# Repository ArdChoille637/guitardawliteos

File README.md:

# GuitarDAWLiteOS

Bare-metal **Raspberry Pi 5** loop recorder / guitarist workbench. I²S audio (PCM1808 ADC + PCM5102A DAC), SD recording, a plain display (no touch) with **5 rotary-encoder knobs + a sustain-pedal footswitch** as the interface — **no OS, no USB in the audio path.** Built on the [Circle](https://github.com/rsta2/circle) bare-metal framework (GPLv3).

> **This is the project front door.** Everything links from here.

## Status — 2026-07-10
- 🎉 **FIRST HARDWARE BOOT — success, first try.** Pi 5 (2GB) booted the M3 audio-engine kernel over HDMI: all 4 cores up, `I2S full duplex (TXRX): RUNNING`, capture counting **exactly 48,000 frames/s**, zero drops, zero ring overruns, storage drain at exactly the audio rate, thermal loop live. Milestone 0 ✅, Spike A ✅ (RP1 proven by the running I²S DMA itself), M3 engine verified live (codecs still to wire).
- ✅ **Research verified.** 29 load-bearing claims checked against primary sources. 6 were wrong; 3 of those change the build. → [docs/claim-verification.md](docs/claim-verification.md)
- ✅ **Spike B done.** Internal MCLK route impossible (`clk_i2s` is claimed by BCLK); an Arduino Nano ESP32 generates 12.2880 MHz instead, bench-verified via its own PCNT peripheral. → [esp32-mclk/](esp32-mclk/)
- ✅ **Milestone 3 code live** — full-duplex I²S monitor path (~1.0 ms worst-case in→out), lock-free SPMC broadcast ring (seqlock reserve/commit; host tests caught a real torn-read bug pre-hardware; passes plain + ThreadSanitizer), 4-core split. Adversarially reviewed (5 lenses, 2 rounds); the review caught a critical `KERNEL_MAX_SIZE` boot-blocker before first boot. → [src/](src/), [tests/](tests/), [planning/build-plan.md](planning/build-plan.md)
- ⏭️ **Next: Milestone 2 wiring** — breadboard the codecs + front-end per [docs/breadboard-build.md](docs/breadboard-build.md) (DAC playback first for the fastest win), Nano ESP32 → PCM1808 SCKI, then the M3 gate: clean tone in→out, 10 min, zero underruns.

## The 6 things verification changed (read before building)
1. **No `≤128` DMA chunk cap** — it's a constructor arg, default **8192**. Ring-buffer/SD batching gets *easier*. The doc was wrong.
2. **Pi 5 SD = BCM2712 SDHCI (`CEMMCDevice`, `0x1000FFF000`), not RP1, not `CSDHCIDevice`.** Tested & supported.
3. **Do NOT add `pciex4_reset=0`** with Circle — Circle brings up the PCIe root complex itself. Stock `config.txt`.
4. **MCLK cannot come from the Pi 5's own GPIO while I²S is running.** `clk_i2s` — the only RP1 clock generator with `pll_audio` as a parent — is already claimed for BCLK. **→ external MCLK generator (Nano ESP32), see Spike B above.**
5. **The two "MIT" libs (simplecodec3, Yin-Pitch-Tracking) are unlicensed** (all-rights-reserved). YIN patent is **expired** → clean-room reimplement from the 2002 paper.
6. **(2026-07-09)** Even the *revised* internal-MCLK mechanism from correction #4 (`clk_i2s→clk_gp0→GPIO4`) turned out to be a resource conflict, not just missing Circle code — see [claim-verification.md](docs/claim-verification.md).

## Hardware (Phase 1)
- Raspberry Pi 5 · microSD (Class-10/UHS-I) · HDMI monitor ≤1080p · USB-serial for the UART debug console.
- PCM1808 ADC (**bus master**, strap-only) · PCM5102A / GY-PCM5102 DAC (strap-only).
- **Arduino Nano ESP32** — external MCLK generator (see [esp32-mclk/](esp32-mclk/)), electrically independent of the Pi 5 except for the MCLK line + shared ground.

**Verified pin map** ([details](planning/build-plan.md#milestone-2--hardware-bring-up-i²s-loopback)) — **the PCM1808 masters the I²S bus** (2026-07-10 pivot: two free-running crystals can't stay fs-locked, so the ADC divides the Nano's MCLK into BCK/LRCK and the Pi runs I²S slave — see [docs/claim-verification.md](docs/claim-verification.md)):

| Source | Signal | → |
|--:|---|---|
| **PCM1808 BCK** | BCLK 3.072 MHz (ADC-driven) | Pi GPIO18 + DAC BCK |
| **PCM1808 LRCK** | LRCLK 48 kHz (ADC-driven) | Pi GPIO19 + DAC LCK |
| PCM1808 DOUT | data IN (capture) | → Pi GPIO20 |
| Pi GPIO21 | data OUT (playback) | → PCM5102A DIN |
| **Nano ESP32 D2/GPIO5** | MCLK 12.288 MHz | → PCM1808 SCKI only |

⚠️ **PCM5102A breakout: set the XSMT pad HIGH (unmute)** — ships muted. ⚠️ **PCM1808: strap MD1=MD0=HIGH (master 256fs), FMT=GND, before power-on** — board-specific pin table in [docs/adc-hookup.md](docs/adc-hookup.md).

## Map
- **[planning/build-plan.md](planning/build-plan.md)** — milestones 0–6, tasks with effort, risk register, pinned dependencies.
- **[docs/claim-verification.md](docs/claim-verification.md)** — full verdict table + 6 consequential corrections with sources.
- **[docs/hardware-review.md](docs/hardware-review.md)** — datasheet-verified BOM, power tree, connection/netlist table, **guitar front-end design**, grounding, risk register.
- **[docs/schematic.md](docs/schematic.md)** — buildable schematic: refdes BOM, net-by-net netlist, **SPICE-verified** front-end, build order, ERC self-check (netlist = rev-A Pi-as-master; see its pivot banner). Sheets: [front-end 5 V](docs/frontend-schematic.svg) · [front-end 9 V TL072 (as-built)](docs/tl072-frontend-schematic.svg) · [codec & clocks (as-built)](docs/codec-power-schematic.svg). Sim: [sim/](docs/sim/).
- **[docs/wiring-diagram.svg](docs/wiring-diagram.svg)** — as-built bench wiring overview (Nano MCLK → PCM1808 **bus master** → Pi 5 slave + PCM5102A; clocks/data/power domains).
- **[kicad/](kicad/)** — openable **KiCad project** (`guitardawliteos.kicad_pro`, KiCad-10-verified) + generated netlist/symbols/BOM from `gen.py` (ERC-checked). See [kicad/README.md](kicad/README.md).
- **[docs/pcb-learning-path.md](docs/pcb-learning-path.md)** — **follow-along PCB-design curriculum + open-hardware roadmap** (M1 board-from-netlist → M4 Pi 5 HAT → M6 rev-B HAT+ → M7 faceplate → M8 retro deck → M9 CM5 carrier), hackability + licensing.
- **[docs/parts-order.md](docs/parts-order.md)** — **DigiKey prototyping order** (verified live 2026-07-01): breadboard + codecs + front-end + tape Level A + Touch Display 2, with MPNs, quantities, substitutions for dead parts, and the not-DigiKey list.
- **[docs/retro-deck-design.md](docs/retro-deck-design.md)** — **Phase-2 architecture (verified; UI pivot 2026-07-23)**: **5 rotary encoders + sustain pedal + display-only panel** (TD2 via `rp1dsi` with `bEnableTouch=FALSE`, zero GPIO — or plain HDMI; SPI TFT ruled out), cassette tape loop as analog insert (Level A ships in rev B, VINR return + REM punch-in), three-layer retro mechanicals, recomputed rev-B GPIO budget (J8 fully allocated + MCP23017 expander).
- **[docs/breadboard-build.md](docs/breadboard-build.md)** + [breadboard-layout.svg](docs/breadboard-layout.svg) — solderless build with the GY modules + a DIP op-amp; placement + step-by-step + gotcha checklist.
- **[docs/adc-hookup.md](docs/adc-hookup.md)** — **bench card: every wire for Pi 5 + PCM1808 + Nano ESP32 capture hookup** (power, ground, straps, clocks, data, order of operations).
- **[docs/tl072-frontend.md](docs/tl072-frontend.md)** — **drawer-parts front-end variant: TL072 on 9 V** (SPICE-verified; two changes from the canonical schematic) + CD4053BE rev-B notes. Schematic sheet: [tl072-frontend-schematic.svg](docs/tl072-frontend-schematic.svg).
- **[docs/build-setup.md](docs/build-setup.md)** — toolchain, build, SD flash, UART.
- **[docs/debug-probe.md](docs/debug-probe.md)** — **Raspberry Pi Debug Probe on the Pi 5**: UART console (mode A) vs. SWD breakpoint debugging of all four cores (mode B), cabling, and the GPIO14/15 conflict with the encoder pinout.
- Original Phase-1 research reference: project `CLAUDE.md` (the GuitarDAWLiteOS research doc).

## Build foundation (pinned)
Circle `develop` @ `22722a7` · `RASPPI=5` → `kernel_2712.img` · FatFs R0.16 (`addon/fatfs`) · YIN clean-room.

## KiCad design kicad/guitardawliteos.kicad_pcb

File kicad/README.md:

# GuitarDAWLiteOS — KiCad project files

> ⚠️ **This netlist is rev-A (Pi-as-master) and predates the 2026-07-10 clock pivot.** `gen.py` still routes
> **MCLK from Pi header pin 7 (GPIO4)** into the PCM1808 SCKI and **straps MD0/MD1 to GND (slave)**. The
> as-built bench is the opposite: **MCLK from the Nano ESP32 D2**, **MD0/MD1 to +3.3 V (ADC = bus master)**,
> Pi = I²S slave. Use this project as a **PCB-design learning vehicle only** — do **not** fab a board from it
> until `gen.py` is re-generated for the pivot (rev-B). The as-built truth is [../docs/adc-hookup.md](../docs/adc-hookup.md)
> + the wiring/codec SVG sheets. "Same I²S/clock topology either way" below refers to the *breadboard vs
> bare-chip* choice, **not** to master/slave — that pivot post-dates this board.

An openable KiCad project for the Phase-1 audio board, plus the generated inputs that feed it.

> **To open in KiCad: open `guitardawliteos.kicad_pro`.** A netlist (`.net`) and a symbol library (`.kicad_sym`) are *not* openable projects — that's why the earlier files wouldn't load. New to this? Read [../docs/pcb-learning-path.md](../docs/pcb-learning-path.md).

| File | What it is |
|------|-----------|
| **`guitardawliteos.kicad_pro`** | **the KiCad project — open THIS** |
| `guitardawliteos.kicad_sch` | schematic (titled blank canvas; draw it per the learning path) |
| `guitardawliteos.kicad_pcb` | board (blank; import the netlist, or lay out from your schematic) |
| `sym-lib-table` | registers the `GuitarDAWLiteOS` symbol lib into the project |
| `gen.py` | generator: defines components + nets, runs ERC-lite, emits the files below. Re-run: `python3 gen.py` |
| `guitardawliteos.net` | **KiCad netlist** (Eeschema export format) — import into the PCB editor |
| `guitardawliteos.kicad_sym` | **custom symbol library** — PCM1808 + PCM5102A (not in stock KiCad libs) |
| `bom.csv` | bill of materials (ref, value, footprint) |
| `validate.py` | parses + schema-checks the `.net` and `.kicad_sym` (stdlib; stands in for `kicad-cli`) |

## What this design is
A **bare-chip carrier board**: discrete **OPA1662** guitar front-end + bare **PCM1808** ADC + bare **PCM5102A** DAC + **AP2112-3.3** LDO + a **2×20 header** to the Pi 5. 41 components, 28 nets. Pinouts are datasheet-verified; the front-end matches [../docs/schematic.md](../docs/schematic.md) and is SPICE-verified.

> **Differs from the breadboard build** ([../docs/breadboard-build.md](../docs/breadboard-build.md)): that one uses the **GY-PCM5102 module** (onboard LDO + output filter). This PCB uses the **bare PCM5102A**, so it includes what the module hides — the AP2112 LDO (5 V→3.3 V), the charge-pump caps (C10/C11 on CAPP/CAPM/VNEG), the LDOO cap (C14), and the output RC (Rol/Col, Ror/Cor). Same I²S/clock/front-end topology either way.

## Use it — two paths

**A. PCB-first (fastest):** the netlist already carries footprints (all stock KiCad libs), so you can skip drawing a schematic.
1. Open `guitardawliteos.kicad_pro` → open the **PCB Editor**.
2. **File → Import → Netlist…** → select `guitardawliteos.net` → *Update PCB*. All 41 parts drop in with footprints + ratsnest.
3. Arrange and route. Keep the analog front-end (U1, J1, the front-end R/C) away from the I²S clocks; single-point star ground; FB1 + C2/C3 right at U2 VCC.

**B. Schematic-first:** to draw the full schematic.
1. **Preferences → Manage Symbol Libraries → add** `guitardawliteos.kicad_sym` (it provides `PCM1808` and `PCM5102A`).
2. Draw using those two symbols + stock `Device:R/C`, `Amplifier_Operational:OPA1662` (or `Device:Opamp_Dual`), `Connector_Generic:Conn_02x20_Odd_Even` (Pi), `Regulator_Linear:AP2112K-3.3`.
3. Annotate → assign footprints (see `bom.csv`) → **Tools → ERC** → generate netlist → PCB.

## Footprints (defaults — reassign freely)
| Part | Footprint |
|------|-----------|
| U1 OPA1662 | `Package_SO:SOIC-8_3.9x4.9mm_P1.27mm` |
| U2 PCM1808 | `Package_SO:TSSOP-14_4.4x5mm_P0.65mm` |
| U3 PCM5102A | `Package_SO:TSSOP-20_4.4x6.5mm_P0.65mm` |
| U4 AP2112-3.3 | `Package_TO_SOT_SMD:SOT-23-5` |
| R / C | `R_0805` / `C_0805` (10 µF/2.2 µF → `C_1206`) |
| RV1 | `Potentiometer_THT:Trimmer_Bourns_3296W_Vertical` |
| J1/J2 | `PinHeader_1x03` (swap for an audio-jack footprint) |
| J3 Pi | `PinHeader_2x20_P2.54mm` |

Prefer hand-soldering? Reassign R/C to `Resistor_THT` / `Capacitor_THT` in the footprint assignment step.

## Notes & caveats
- **gen.py ERC-lite** checks: every component pin on exactly one net, every net ≥2 nodes, unique refs, footprints present, s-expr balanced. It is clean (it caught two real omissions during authoring — PCM5102A FMT and an unused Pi 3V3 pin). `python3 validate.py` re-parses + schema-checks the outputs (41 components / 28 nets / 129 nodes / 2 symbols — all resolve). Still run **KiCad's own ERC** after drawing the schematic.
- **Validation status: ✅ KiCad-verified.** `kicad-cli` (KiCad **10.0.4**) loaded the symbol library via `sym upgrade` (parsed + re-saved, no warnings) and `sym export svg` rendered both `PCM1808` and `PCM5102A` with all pin names — so the symbols open cleanly in KiCad. The netlist is schema-checked by `validate.py` (41 comp / 28 nets / 129 nodes, all refs resolve); KiCad imports netlists only through the Pcbnew GUI (no CLI path), so confirm that import in the app. The committed `.kicad_sym` uses the portable `20211014` format (reads in KiCad 6–10).
- The Pi header's **3V3 pin is intentionally unused** — this board makes its own 3.3 V via U4 (so don't also wire Pi 3V3 in).
- U4 **EN (pin 3) is tied to VIN** (always enabled).
- Confirm your exact op-amp's pinout matches the standard dual layout (1=OUTA…8=V+) before committing copper.
- This is a **netlist + symbols**, not a finished PCB layout — placement/routing is yours (see the breadboard guide for the placement strategy, which applies to the PCB too).

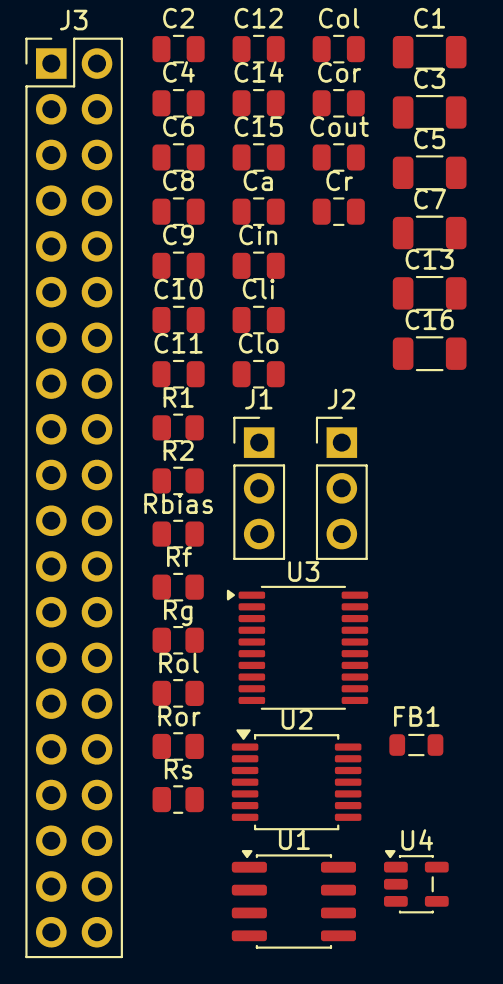
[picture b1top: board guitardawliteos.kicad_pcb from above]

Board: 2 copper layers, 40 parts (0 on the bottom side), 27 nets, no tracks yet.

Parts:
C1, C3, C5, C7, C13, C16: 10uF; C_1206_3216Metric
C2, C4, C6, C8, C9, C12, C14, C15: 0.1uF; C_0805_2012Metric
C10, C11: 2.2uF; C_0805_2012Metric
Ca: 1nF; C_0805_2012Metric
Cin: 0.1uF; C_0805_2012Metric
Cli: 1uF; C_0805_2012Metric
Clo: 1uF; C_0805_2012Metric
Col: 2.2nF; C_0805_2012Metric
Cor: 2.2nF; C_0805_2012Metric
Cout: 1uF; C_0805_2012Metric
Cr: 1uF; C_0805_2012Metric
FB1: FerriteBead; L_0805_2012Metric
J1: Guitar_6.35mm; PinHeader_1x03_P2.54mm_Vertical
J2: Line_out; PinHeader_1x03_P2.54mm_Vertical
J3: RPi5_GPIO; PinHeader_2x20_P2.54mm_Vertical
R1, R2: 10k; R_0805_2012Metric
Rbias: 1M; R_0805_2012Metric
Rf: 10k; R_0805_2012Metric
Rg: 10k; R_0805_2012Metric
Rol: 470; R_0805_2012Metric
Ror: 470; R_0805_2012Metric
Rs: 1k; R_0805_2012Metric
U1: OPA1662; SOIC-8_3.9x4.9mm_P1.27mm
U2: PCM1808; TSSOP-14_4.4x5mm_P0.65mm
U3: PCM5102A; TSSOP-20_4.4x6.5mm_P0.65mm
U4: AP2112K-3.3; SOT-23-5

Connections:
+3V3: C4.1, C5.1, C9.1, C12.1, C13.1, C15.1, C16.1, Clo.1, U2.4, U3.1, U3.8, U3.17, U3.20, U4.5
+5V: C8.1, Cli.1, FB1.1, J3.2, R1.1, U1.8, U4.1, U4.3
AAO: Cout.2, Rs.1
BCLK: J3.12, U2.8, U3.13
BUF: U1.1, U1.2, U1.5
CAPDAT: J3.38, U2.9
CPM: C10.2, U3.4
CPP: C10.1, U3.2
FEO: Cout.1, U1.7
GIN: Cin.1, J1.1
GND: C1.2, C2.2, C3.2, C4.2, C5.2, C6.2, C7.2, C8.2, C9.2, C11.2, C12.2, C13.2, C14.2, C15.2, C16.2, Ca.2, Cli.2, Clo.2, Col.2, Cor.2, Cr.2, J1.2, J1.3, J2.3, J3.6, R2.2, U1.4, U2.2, U2.5, U2.10, U2.11, U2.12, U3.3, U3.9, U3.10, U3.11, U3.12, U3.16, U3.19, U4.2, U4.4
LDOO: C14.1, U3.18
LOUT: Col.1, J2.1, Rol.2
LRCLK: J3.35, U2.7, U3.15
MCLK: J3.7, U2.6
NBI: Cin.2, Rbias.2, U1.3
NINV: Rf.1, Rg.1, U1.6
OUTL: Rol.1, U3.6
OUTR: Ror.1, U3.7
PLAYDAT: J3.40, U3.14
ROUT: Cor.1, J2.2, Ror.2
VBIAS: C1.1, R1.2, R2.1, Rbias.1, Rg.2
VCC_A: C2.1, C3.1, FB1.2, U2.3
VINL: Ca.1, Rs.2, U2.13
VINR: Cr.1, U2.14
VNEG: C11.1, U3.5
VREF: C6.1, C7.1, U2.1

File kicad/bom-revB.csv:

Ref,Value,Footprint
C1,10uF,Capacitor_SMD:C_1206_3216Metric
C10,2.2uF,Capacitor_SMD:C_0805_2012Metric
C11,2.2uF,Capacitor_SMD:C_0805_2012Metric
C12,0.1uF,Capacitor_SMD:C_0805_2012Metric
C13,10uF,Capacitor_SMD:C_1206_3216Metric
C14,0.1uF,Capacitor_SMD:C_0805_2012Metric
C15,0.1uF,Capacitor_SMD:C_0805_2012Metric
C16,10uF,Capacitor_SMD:C_1206_3216Metric
C2,0.1uF,Capacitor_SMD:C_0805_2012Metric
C3,10uF,Capacitor_SMD:C_1206_3216Metric
C4,0.1uF,Capacitor_SMD:C_0805_2012Metric
C5,10uF,Capacitor_SMD:C_1206_3216Metric
C6,0.1uF,Capacitor_SMD:C_0805_2012Metric
C7,10uF,Capacitor_SMD:C_1206_3216Metric
C8,0.1uF,Capacitor_SMD:C_0805_2012Metric
C9,0.1uF,Capacitor_SMD:C_0805_2012Metric
Ca,1nF,Capacitor_SMD:C_0805_2012Metric
Cin,0.1uF,Capacitor_SMD:C_0805_2012Metric
Col,2.2nF,Capacitor_SMD:C_0805_2012Metric
Cor,2.2nF,Capacitor_SMD:C_0805_2012Metric
Cout,1uF,Capacitor_SMD:C_0805_2012Metric
Cr,1uF,Capacitor_SMD:C_0805_2012Metric
FB1,FerriteBead,Inductor_SMD:L_0805_2012Metric
J1,Guitar_6.35mm,Connector_PinHeader_2.54mm:PinHeader_1x03_P2.54mm_Vertical
J2,Line_out,Connector_PinHeader_2.54mm:PinHeader_1x03_P2.54mm_Vertical
J3,RPi5_GPIO,Connector_PinHeader_2.54mm:PinHeader_2x20_P2.54mm_Vertical
J4,Nano_ESP32_MCLK,Connector_PinHeader_2.54mm:PinHeader_1x03_P2.54mm_Vertical
R1,10k,Resistor_SMD:R_0805_2012Metric
R2,10k,Resistor_SMD:R_0805_2012Metric
RV1,100k,Potentiometer_THT:Trimmer_Bourns_3296W_Vertical
R_mclk,33,Resistor_SMD:R_0805_2012Metric
Rbias,1M,Resistor_SMD:R_0805_2012Metric
Rf,10k,Resistor_SMD:R_0805_2012Metric
Rg,10k,Resistor_SMD:R_0805_2012Metric
Rol,470,Resistor_SMD:R_0805_2012Metric
Ror,470,Resistor_SMD:R_0805_2012Metric
Rs,1k,Resistor_SMD:R_0805_2012Metric
U1,OPA1662,Package_SO:SOIC-8_3.9x4.9mm_P1.27mm
U2,PCM1808,Package_SO:TSSOP-14_4.4x5mm_P0.65mm
U3,PCM5102A,Package_SO:TSSOP-20_4.4x6.5mm_P0.65mm
